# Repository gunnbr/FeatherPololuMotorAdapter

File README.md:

# FeatherPololuMotorAdapter
Adapts a Feather Motor Shield to easily connect to Pololu motors with encoders using a 6 pin header

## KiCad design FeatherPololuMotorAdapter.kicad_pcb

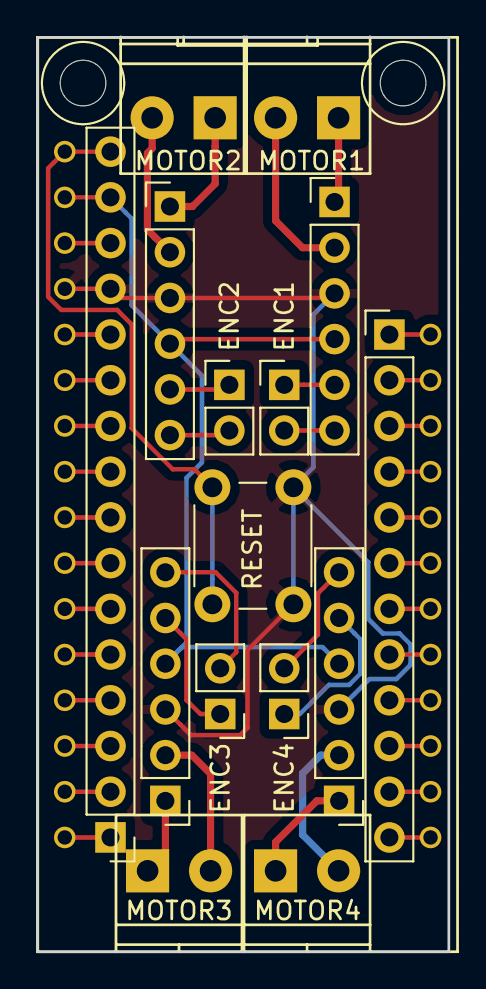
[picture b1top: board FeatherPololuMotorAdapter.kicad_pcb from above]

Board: 2 copper layers, 22.9 x 50.8 mm, 16 parts (0 on the bottom side), 44 nets.

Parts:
P1: MOTOR1; Pin_Header_Straight_1x06_Pitch2.54mm
P2: MOTOR1; TerminalBlock_Pheonix_PT-3.5mm_2pol
P3: ENC1; Pin_Header_Straight_1x02_Pitch2.54mm
P4: CONN_01X16; Pin_Header_Straight_1x16_Pitch2.54mm
P5: MOTOR2; Pin_Header_Straight_1x06_Pitch2.54mm
P6: MOTOR2; TerminalBlock_Pheonix_PT-3.5mm_2pol
P7: ENC2; Pin_Header_Straight_1x02_Pitch2.54mm
P8: MOTOR3; Pin_Header_Straight_1x06_Pitch2.54mm
P9: MOTOR3; TerminalBlock_Pheonix_PT-3.5mm_2pol
P10: ENC3; Pin_Header_Straight_1x02_Pitch2.54mm
P11: CONN_01X12; Pin_Header_Straight_1x12_Pitch2.54mm
P12: MOTOR4; Pin_Header_Straight_1x06_Pitch2.54mm
P13: MOTOR4; TerminalBlock_Pheonix_PT-3.5mm_2pol
P14: ENC4; Pin_Header_Straight_1x02_Pitch2.54mm
SW1: RESET; SW_PUSH_6mm
U1: GenericFeather; Adafruit_Feather

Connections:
/RESET: P4.16, SW1.1, U1.1
ENC1_A: P1.5, P3.1
ENC1_B: P1.6, P3.2
ENC2_A: P5.5, P7.1
ENC2_B: P5.6, P7.2
ENC3_A: P8.5, P10.1
ENC3_B: P8.6, P10.2
ENC4_A: P12.5, P14.1
ENC4_B: P12.6, P14.2
ENC_GND: P1.3, P4.13, P5.3, P8.3, P12.3, SW1.2, U1.4
ENC_VCC: P1.4, P4.15, P5.4, P8.4, P12.4, U1.2
M1_V+: P1.1, P2.1
M1_V-: P1.2, P2.2
M2_V+: P5.1, P6.1
M2_V-: P5.2, P6.2
M3_V+: P8.1, P9.1
M3_V-: P8.2, P9.2
M4_V+: P12.1, P13.1
M4_V-: P12.2, P13.2
unnamed: P4.1, U1.16
unnamed: P4.2, U1.15
unnamed: P4.3, U1.14
unnamed: P4.4, U1.13
unnamed: P4.5, U1.12
unnamed: P4.6, U1.11
unnamed: P4.7, U1.10
unnamed: P4.8, U1.9
unnamed: P4.9, U1.8
unnamed: P4.10, U1.7
unnamed: P4.11, U1.6
unnamed: P4.12, U1.5
unnamed: P4.14, U1.3
unnamed: P11.1, U1.28
unnamed: P11.2, U1.27
unnamed: P11.3, U1.26
unnamed: P11.4, U1.25
unnamed: P11.5, U1.24
unnamed: P11.6, U1.23
unnamed: P11.7, U1.22
unnamed: P11.8, U1.21
unnamed: P11.9, U1.20
unnamed: P11.10, U1.19
unnamed: P11.11, U1.18
unnamed: P11.12, U1.17

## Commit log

2017-05-15 Initial checkin
    Main components on the board except for the feather itself, which is
    giving me trouble importing the library.
2017-05-15 Added generic feather component.
    Stil working on schematic.
2017-05-15 Ignore the .bak files.
2017-05-16 Finished schematic. Started work on layout.
2017-05-19 Finished schematic and layout.
